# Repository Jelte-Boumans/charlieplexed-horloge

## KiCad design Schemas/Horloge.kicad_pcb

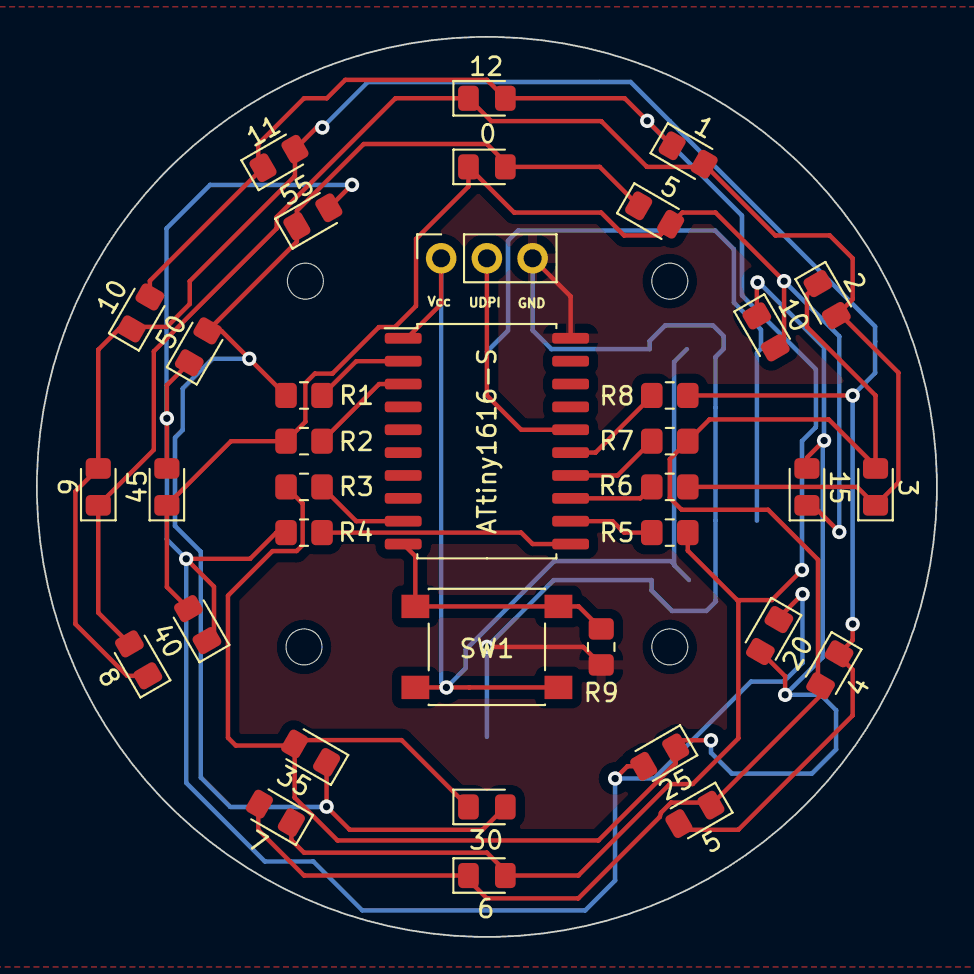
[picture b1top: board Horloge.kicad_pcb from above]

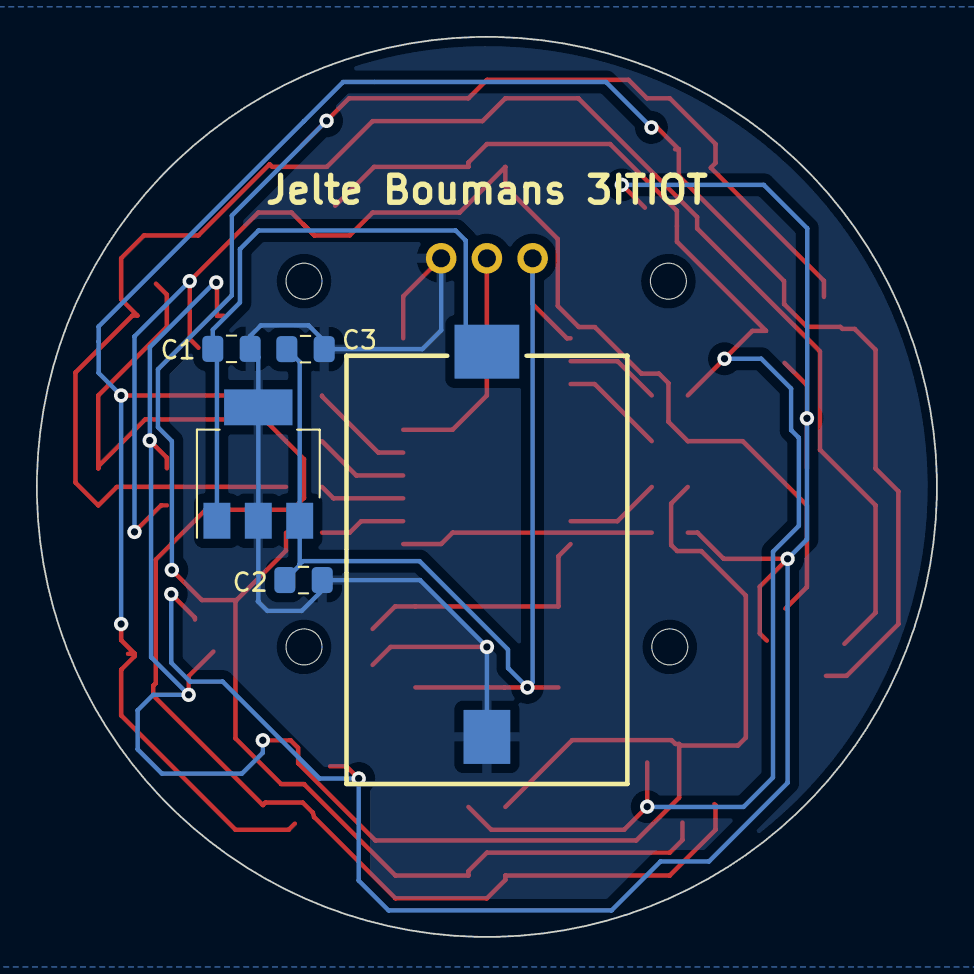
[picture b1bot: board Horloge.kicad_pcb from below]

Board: 2 copper layers, 50.0 x 50.0 mm, 41 parts (5 on the bottom side), 21 nets.

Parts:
0, 1, 2, 3, 4, 5, 5#2, 6, 7, 8, 9, 10, 10#2, 11, 12, 15, 20, 25, 30, 35, 40, 45, 50, 55: LED; LED_0805_2012Metric_Pad1.15x1.40mm_HandSolder
BTe: Battery_Cell; S8421-45R_1
C1, C2: 1uF; C_0805_2012Metric_Pad1.18x1.45mm_HandSolder
C3: 100nF; C_0805_2012Metric_Pad1.18x1.45mm_HandSolder
J1: Conn_01x03_Female; PinSocket_1x03_P2.54mm_Vertical
R1, R2, R3, R4: 120Ω; R_0805_2012Metric_Pad1.20x1.40mm_HandSolder
R5, R6, R7, R8: 150Ω; R_0805_2012Metric_Pad1.20x1.40mm_HandSolder
R9: 1kΩ; R_0805_2012Metric_Pad1.20x1.40mm_HandSolder
SW1: SW_Push; SW_Push_1P1T_NO_6x6mm_H9.5mm
U1: ATtiny1616-S; SOIC-20W_7.5x12.8mm_P1.27mm
U2: AP7361C-33E; SOT-223-3_TabPin2

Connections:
GND: BTe.2 (-), C1.2, C2.2, C3.2, J1.3, R9.2, U1.20 (GND), U2.2 (GND)
unnamed: BTe.1 (+), C1.1, U2.1 (VI)
unnamed: 0.1 (K), 5#2.2 (A), 10#2.2 (A), 15.1 (K), 40.2 (A), 45.1 (K), R2.1
unnamed: 0.2 (A), 5#2.1 (K), 30.2 (A), 35.1 (K), 50.2 (A), 55.1 (K), R1.1
unnamed: 10#2.1 (K), 15.2 (A), 20.2 (A), 25.1 (K), 30.1 (K), 35.2 (A), R3.1
unnamed: 20.1 (K), 25.2 (A), 40.1 (K), 45.2 (A), 50.1 (K), 55.2 (A), R4.1
unnamed: 1.2 (A), 2.2 (A), 3.1 (K), 8.2 (A), 9.1 (K), 12.1 (K), R6.1
unnamed: 1.1 (K), 6.2 (A), 7.1 (K), 10.2 (A), 11.1 (K), 12.2 (A), R5.1
unnamed: 2.1 (K), 3.2 (A), 4.2 (A), 5.1 (K), 6.1 (K), 7.2 (A), R7.1
unnamed: 4.1 (K), 5.2 (A), 8.1 (K), 9.2 (A), 10.1 (K), 11.2 (A), R8.1
PA0 UDPI: J1.2, U1.16 (~RESET/PA0)
PA4~: R1.2, U1.2 (PA4)
PA5~: R2.2, U1.3 (PA5)
PB0~: R4.2, U1.11 (PB0)
PB1: R9.1, SW1.1, U1.10 (PB1)
PB2~: R3.2, U1.9 (PB2)
PC0: R5.2, U1.12 (PC0)
PC1: R6.2, U1.13 (PC1)
PC2: R7.2, U1.14 (PC2)
PC3: R8.2, U1.15 (PC3)
Vcc: C2.1, C3.1, J1.1, SW1.2, U1.1 (VCC), U2.3 (VO)

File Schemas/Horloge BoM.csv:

"Id";"Designator";"Package";"Quantity";"Designation";"Supplier and ref";
1;"20,25,1,55,0,50,5,35,45,40,8,11,7,3,10,30,12,6,4,2,5,10,9,15";"LED_0805_2012Metric_Pad1.15x1.40mm_HandSolder";24;"LED";;;
2;"R4,R2,R3,R1";"R_0805_2012Metric_Pad1.20x1.40mm_HandSolder";4;"120Ω";;;
3;"U1";"SOIC-20W_7.5x12.8mm_P1.27mm";1;"ATtiny1616-S";;;
4;"R6,R5,R8,R7";"R_0805_2012Metric_Pad1.20x1.40mm_HandSolder";4;"150Ω";;;
5;"R9";"R_0805_2012Metric_Pad1.20x1.40mm_HandSolder";1;"1kΩ";;;
6;"J1";"PinSocket_1x03_P2.54mm_Vertical";1;"Conn_01x03_Female";;;
7;"SW1";"SW_Push_1P1T_NO_6x6mm_H9.5mm";1;"SW_Push";;;
8;"C3";"C_0805_2012Metric_Pad1.18x1.45mm_HandSolder";1;"100nF";;;
9;"C2,C1";"C_0805_2012Metric_Pad1.18x1.45mm_HandSolder";2;"1uF";;;
10;"BTe";"S8421-45R_1";1;"Battery_Cell";;;
11;"U2";"SOT-223-3_TabPin2";1;"AP7361C-33E";;;
